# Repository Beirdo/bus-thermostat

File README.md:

# bus-thermostat
Interface to connect a standard thermostat to a Webasto Thermo Top C for my bus

60Hz oscillator design inspired by https://www.youtube.com/watch?v=BfqGnwAhldA

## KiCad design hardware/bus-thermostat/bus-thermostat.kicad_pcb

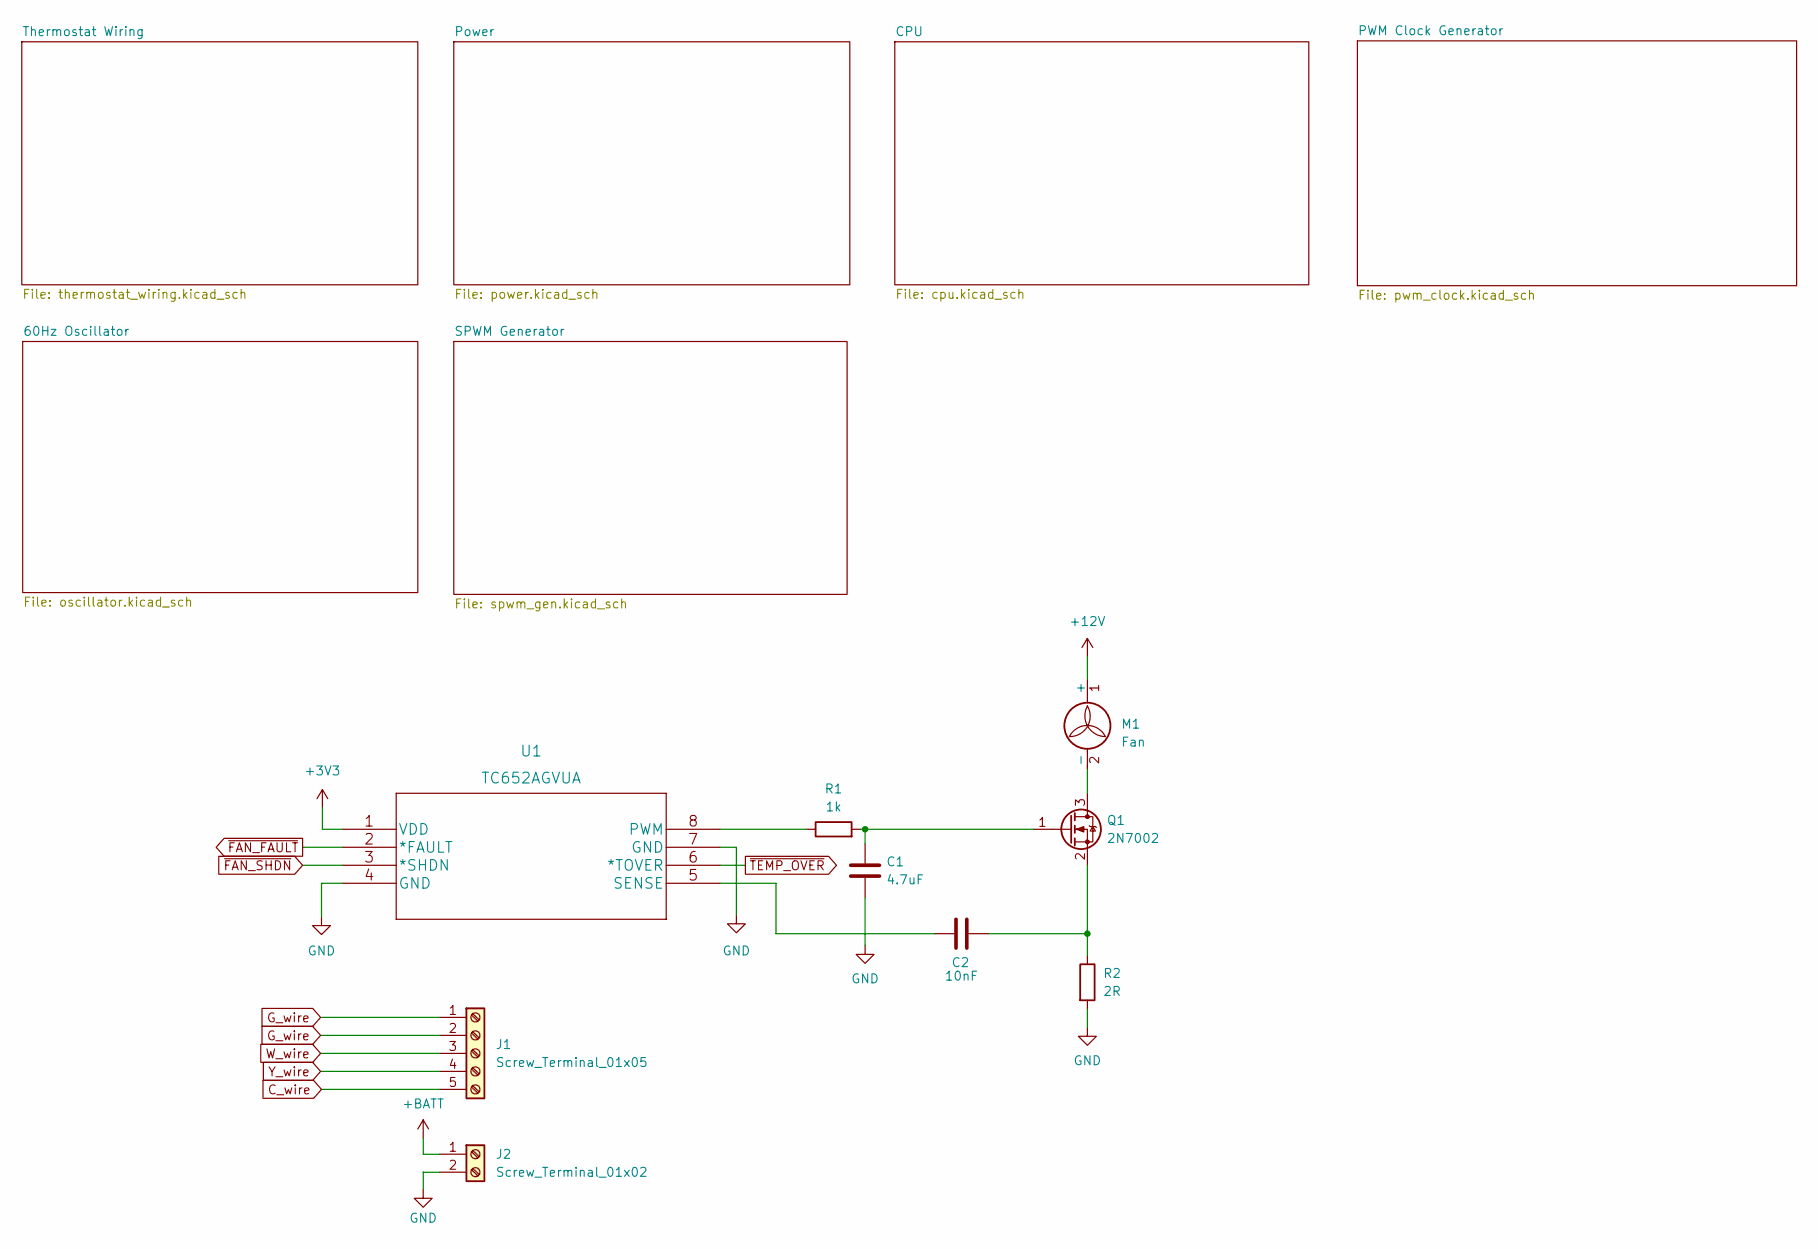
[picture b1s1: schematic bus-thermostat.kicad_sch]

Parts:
C1: 4.7uF; C_0805_2012Metric_Pad1.18x1.45mm_HandSolder
C2: 10nF; C_0805_2012Metric_Pad1.18x1.45mm_HandSolder
J1: Screw_Terminal_01x05; TerminalBlock_TE_282834-5_1x05_P2.54mm_Horizontal
J2: Screw_Terminal_01x02; TerminalBlock_TE_282834-2_1x02_P2.54mm_Horizontal
M1: Fan; PinHeader_1x02_P1.00mm_Vertical
Q1: 2N7002; SOT-23
R1: 1k; R_0805_2012Metric_Pad1.20x1.40mm_HandSolder
R2: 2R; R_0805_2012Metric_Pad1.20x1.40mm_HandSolder
U1: TC652AGVUA

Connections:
+3V3: U1.1 (VDD); also elsewhere on the board
+12V: M1.1 (+); also elsewhere on the board
+BATT: J2.1; also elsewhere on the board
C_wire: J1.5; also elsewhere on the board
GND: C1.2, J2.2, R2.2, U1.4 (GND), U1.7 (GND); also elsewhere on the board
G_wire: J1.2; also elsewhere on the board
unnamed: C1.1, Q1.1 (G), R1.2
unnamed: C2.1, U1.5 (SENSE)
unnamed: C2.2, Q1.2 (S), R2.1
unnamed: M1.2 (-), Q1.3 (D)
unnamed: R1.1, U1.8 (PWM)
W_wire: J1.3; also elsewhere on the board
Y_wire: J1.4; also elsewhere on the board
~FAN_FAULT: U1.2 (*FAULT); also elsewhere on the board
~FAN_SHDN: U1.3 (*SHDN); also elsewhere on the board
~TEMP_OVER: U1.6 (*TOVER); also elsewhere on the board

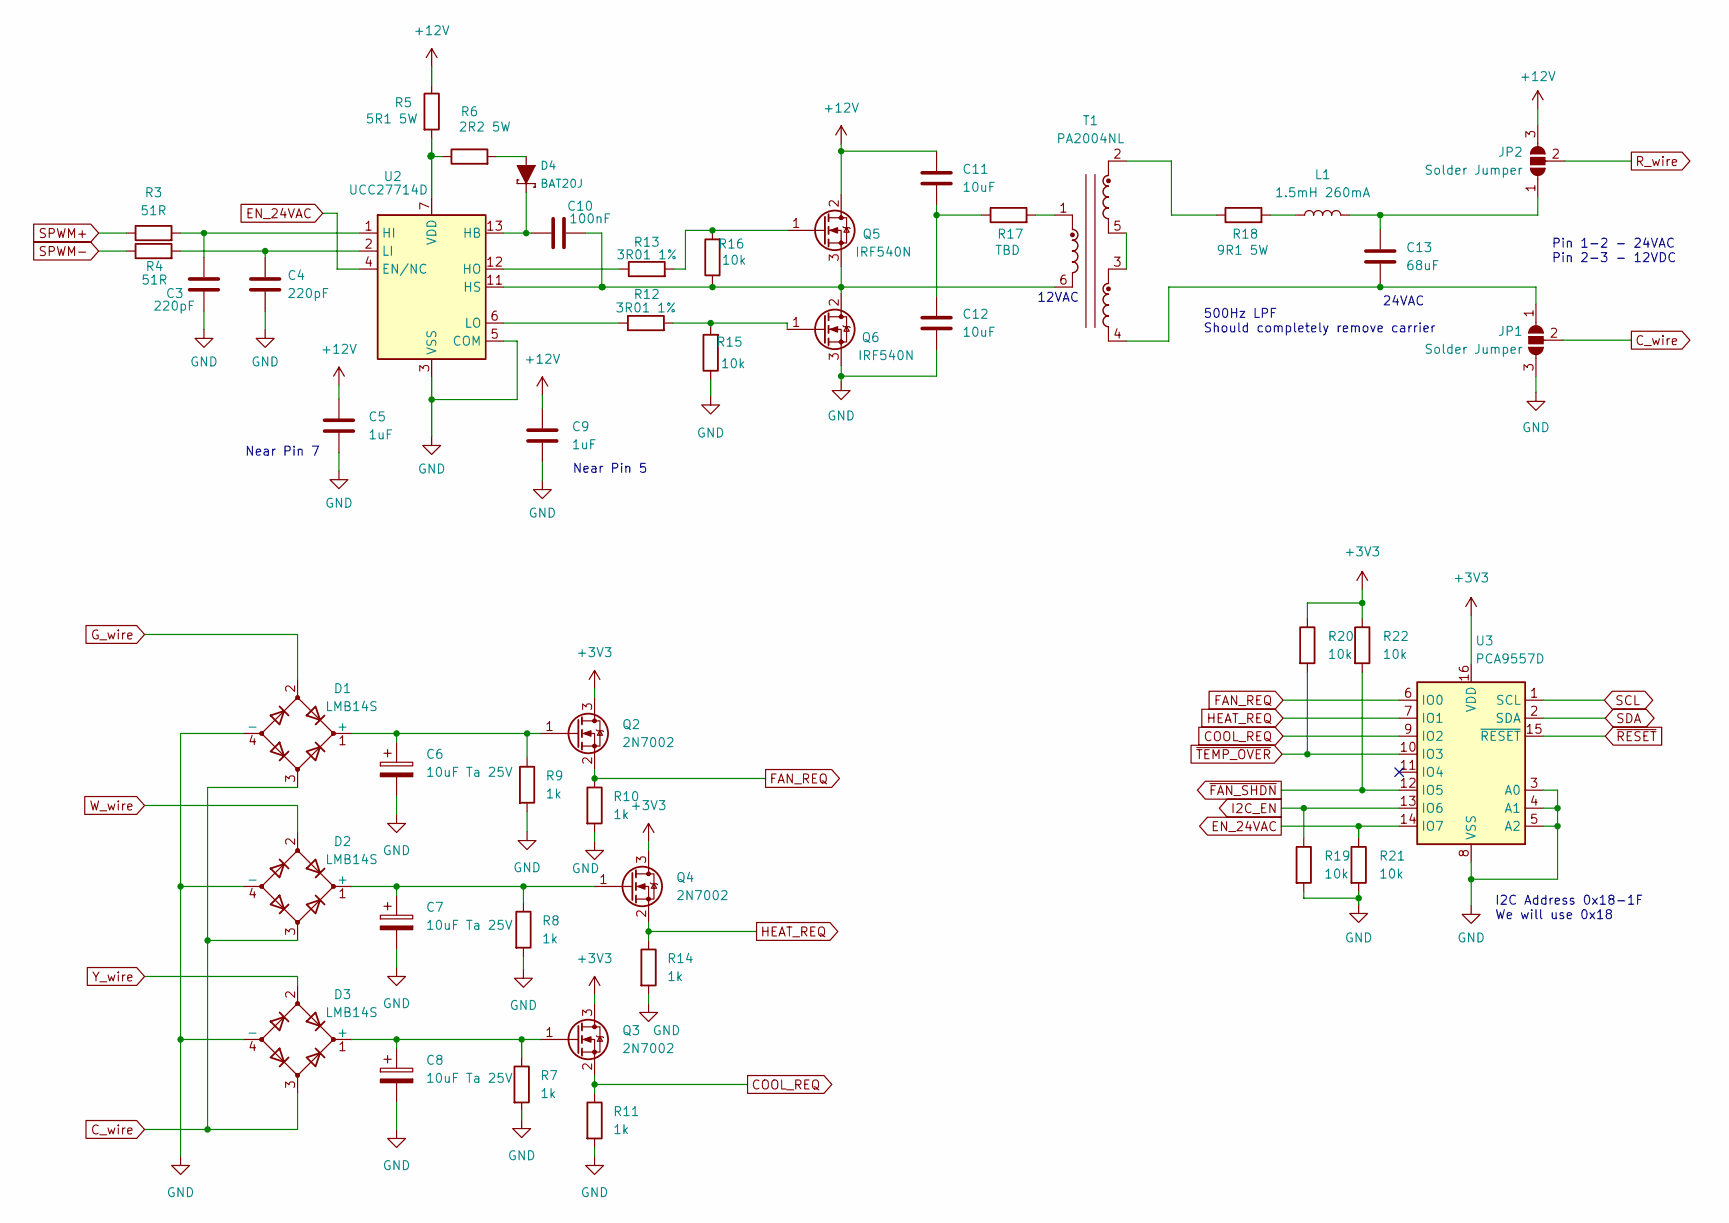
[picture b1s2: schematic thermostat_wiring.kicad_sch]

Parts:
C3, C4: 220pF; C_0805_2012Metric_Pad1.18x1.45mm_HandSolder
C5, C9: 1uF; C_0805_2012Metric_Pad1.18x1.45mm_HandSolder
C6, C7, C8: 10uF Ta 25V; CP_EIA-6032-20_AVX-F_Pad2.25x2.35mm_HandSolder
C10: 100nF; C_0805_2012Metric_Pad1.18x1.45mm_HandSolder
C11, C12: 10uF; C_0805_2012Metric_Pad1.18x1.45mm_HandSolder
C13: 68uF; C_0805_2012Metric_Pad1.18x1.45mm_HandSolder
D1, D2, D3: LMB14S; Diode_Bridge_Vishay_MBLS
D4: BAT20J; SOD-323
JP1, JP2: Solder Jumper; SolderJumper-3_P2.0mm_Open_TrianglePad1.0x1.5mm
L1: 1.5mH 260mA; L_Radial_D28.0mm_P29.20mm
Q2, Q3, Q4: 2N7002; SOT-23
Q5, Q6: IRF540N; TO-220-3_Vertical
R3, R4: 51R; R_0805_2012Metric_Pad1.20x1.40mm_HandSolder
R5: 5R1 5W; 355010RFT
R6: 2R2 5W; 355010RFT
R7, R8, R9, R10, R11, R14: 1k; R_0805_2012Metric_Pad1.20x1.40mm_HandSolder
R12, R13: 3R01 1%; R_0805_2012Metric_Pad1.20x1.40mm_HandSolder
R15, R16, R19, R20, R21, R22: 10k; R_0805_2012Metric_Pad1.20x1.40mm_HandSolder
R17: TBD; R_0805_2012Metric_Pad1.20x1.40mm_HandSolder
R18: 9R1 5W; 355010RFT
T1: PA2004NL; Pulse_PA2004NL
U2: UCC27714D; SOIC-14_3.9x8.7mm_P1.27mm
U3: PCA9557D; SOP-16_3.9x9.9mm_P1.27mm

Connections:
+3V3: Q2.3 (D), Q3.3 (D), Q4.3 (D), R20.1, R22.1, U3.16 (VDD); also elsewhere on the board
+12V: C5.1, C9.1, C11.1, JP2.3 (B), Q5.2 (D), R5.1; also elsewhere on the board
COOL_REQ: Q3.2 (S), R11.1, U3.9 (IO2)
C_wire: D1.3, D2.3, D3.3, JP1.2 (C); also elsewhere on the board
EN_24VAC: R21.1, U2.4 (EN/NC), U3.14 (IO7)
FAN_REQ: Q2.2 (S), R10.1, U3.6 (IO0)
GND: C3.2, C4.2, C5.2, C6.2, C7.2, C8.2, C9.2, C12.2, D1.4 (-), D2.4 (-), D3.4 (-), JP1.3 (B), Q6.3 (S), R7.2, R8.2, R9.2, R10.2, R11.2, R14.2, R15.1, R19.2, R21.2, U2.3 (VSS), U2.5 (COM), U3.3 (A0), U3.4 (A1), U3.5 (A2), U3.8 (VSS); also elsewhere on the board
G_wire: D1.2; also elsewhere on the board
HEAT_REQ: Q4.2 (S), R14.1, U3.7 (IO1)
I2C_EN: R19.1, U3.13 (IO6); also elsewhere on the board
unnamed: C3.1, R3.2, U2.1 (HI)
unnamed: C4.1, R4.2, U2.2 (LI)
unnamed: C6.1, D1.1 (+), Q2.1 (G), R9.1
unnamed: C7.1, D2.1 (+), Q4.1 (G), R8.1
unnamed: C8.1, D3.1 (+), Q3.1 (G), R7.1
unnamed: C10.1, D4.C, U2.13 (HB)
unnamed: C10.2, U2.11 (HS)
unnamed: C11.2, C12.1, R17.1
unnamed: C13.1, JP2.1 (A), L1.2
unnamed: C13.2, JP1.1 (A), T1.4
unnamed: D4.A, R6.2
unnamed: L1.1, R18.2
unnamed: Q5.1 (G), R13.2, R16.2
unnamed: Q5.3 (S), Q6.2 (D), R16.1, T1.6
unnamed: Q6.1 (G), R12.2, R15.2
unnamed: R5.2, R6.1, U2.7 (VDD)
unnamed: R12.1, U2.6 (LO)
unnamed: R13.1, U2.12 (HO)
unnamed: R17.2, T1.1
unnamed: R18.1, T1.2
unnamed: T1.3, T1.5
R_wire: JP2.2 (C)
SCL: U3.1 (SCL); also elsewhere on the board
SDA: U3.2 (SDA); also elsewhere on the board
SPWM+: R3.1; also elsewhere on the board
SPWM-: R4.1; also elsewhere on the board
W_wire: D2.2; also elsewhere on the board
Y_wire: D3.2; also elsewhere on the board
~FAN_SHDN: R22.2, U3.12 (IO5); also elsewhere on the board
~RESET: U3.15 (~RESET); also elsewhere on the board
~TEMP_OVER: R20.2, U3.10 (IO3); also elsewhere on the board

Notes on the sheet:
Near Pin 5
Pin 1-2 - 24VAC Pin 2-3 - 12VDC
500Hz LPF Should completely remove carrier
12VAC
Near Pin 7
24VAC
I2C Address 0x18-1F We will use 0x18

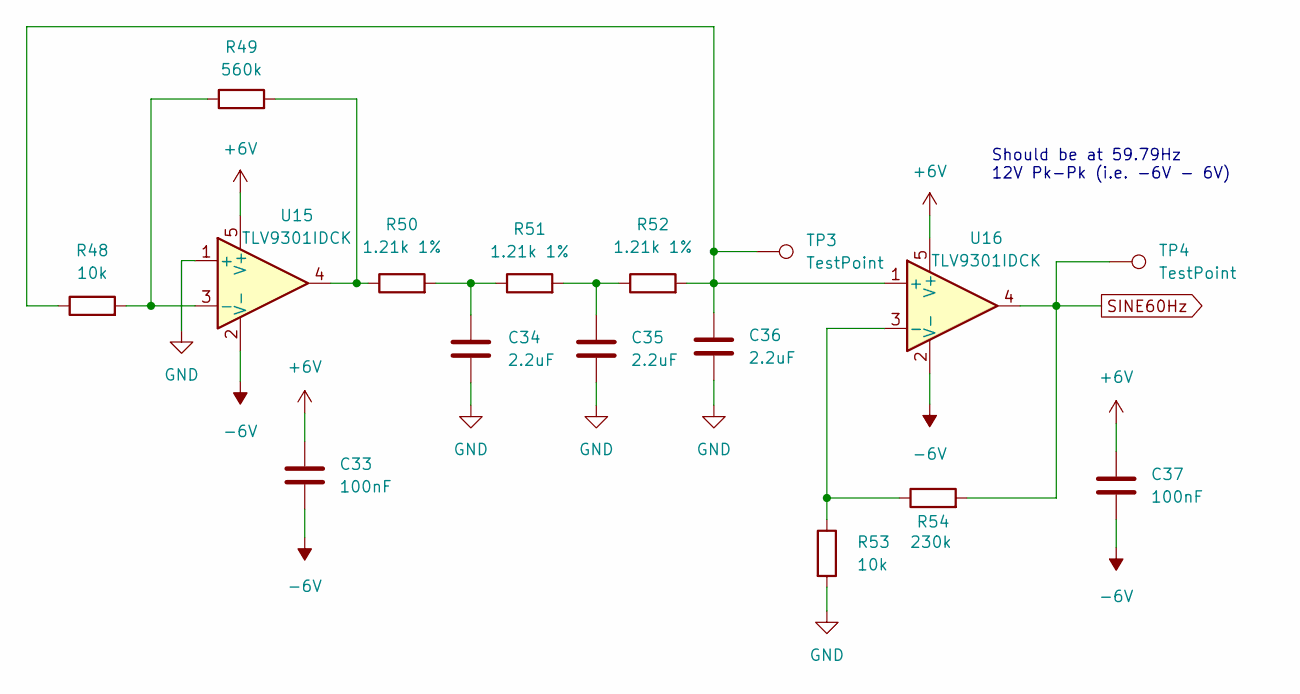
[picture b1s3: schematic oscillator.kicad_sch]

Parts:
C33, C37: 100nF; C_0805_2012Metric_Pad1.18x1.45mm_HandSolder
C34, C35, C36: 2.2uF; C_0805_2012Metric_Pad1.18x1.45mm_HandSolder
R48, R53: 10k; R_0805_2012Metric_Pad1.20x1.40mm_HandSolder
R49: 560k; R_0805_2012Metric_Pad1.20x1.40mm_HandSolder
R50, R51, R52: 1.21k 1%; R_0805_2012Metric_Pad1.20x1.40mm_HandSolder
R54: 230k; R_0805_2012Metric_Pad1.20x1.40mm_HandSolder
TP3, TP4: TestPoint; Pin_D0.7mm_L6.5mm_W1.8mm_FlatFork
U15, U16: TLV9301IDCK; SOT-353_SC-70-5

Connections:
+6V: C33.1, C37.1, U15.5 (V+), U16.5 (V+); also elsewhere on the board
-6V: C33.2, C37.2, U15.2 (V-), U16.2 (V-); also elsewhere on the board
GND: C34.1, C35.1, C36.1, R53.2, U15.1 (+); also elsewhere on the board
unnamed: C34.2, R50.2, R51.1
unnamed: C35.2, R51.2, R52.1
unnamed: C36.2, R48.1, R52.2, TP3.1, U16.1 (+)
unnamed: R48.2, R49.1, U15.3 (-)
unnamed: R49.2, R50.1, U15.4
unnamed: R53.1, R54.1, U16.3 (-)
SINE60Hz: R54.2, TP4.1, U16.4; also elsewhere on the board

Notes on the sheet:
Should be at 59.79Hz 12V Pk-Pk (i.e. -6V - 6V)

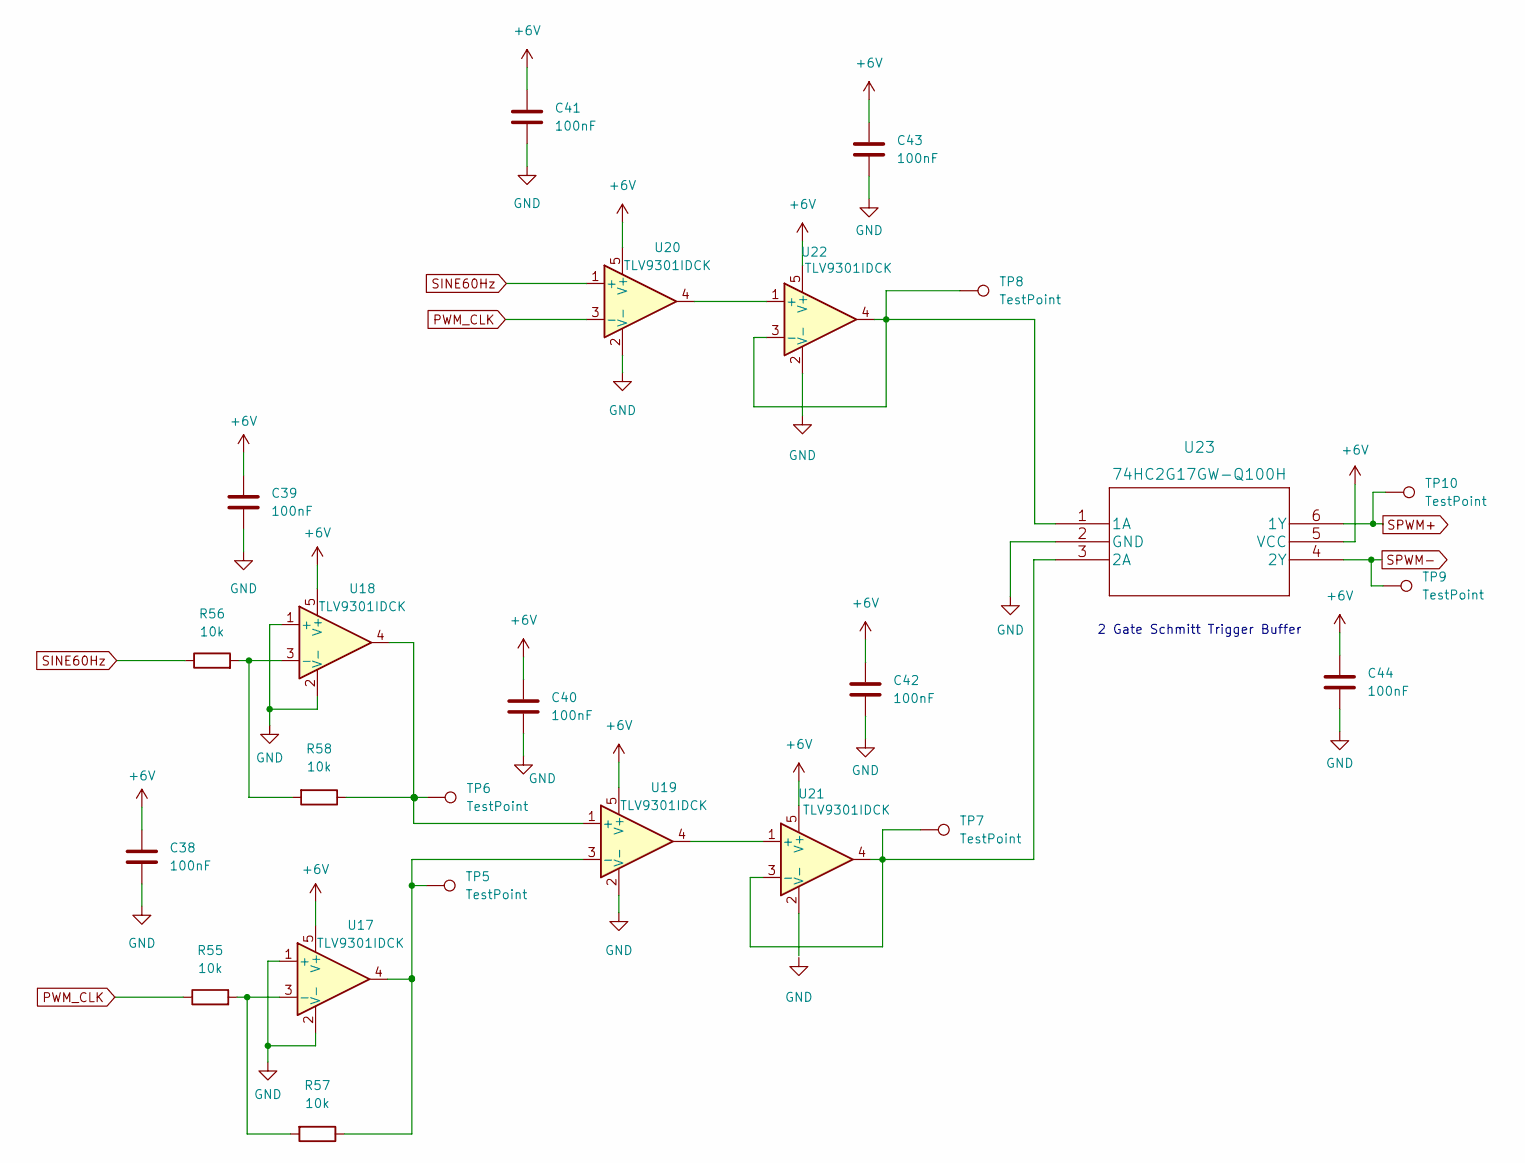
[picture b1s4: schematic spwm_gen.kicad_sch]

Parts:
C38, C39, C40, C41, C42, C43, C44: 100nF; C_0805_2012Metric_Pad1.18x1.45mm_HandSolder
R55, R56, R57, R58: 10k; R_0805_2012Metric_Pad1.20x1.40mm_HandSolder
TP5, TP6, TP7, TP8, TP9, TP10: TestPoint; Pin_D0.7mm_L6.5mm_W1.8mm_FlatFork
U17, U18, U19, U20, U21, U22: TLV9301IDCK; SOT-353_SC-70-5
U23: 74HC2G17GW-Q100H

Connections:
+6V: C38.1, C39.1, C40.1, C41.1, C42.1, C43.1, C44.1, U17.5 (V+), U18.5 (V+), U19.5 (V+), U20.5 (V+), U21.5 (V+), U22.5 (V+), U23.5 (VCC); also elsewhere on the board
GND: C38.2, C39.2, C40.2, C41.2, C42.2, C43.2, C44.2, U17.1 (+), U17.2 (V-), U18.1 (+), U18.2 (V-), U19.2 (V-), U20.2 (V-), U22.2 (V-), U23.2 (GND); also elsewhere on the board
unnamed: R55.2, R57.2, U17.3 (-)
unnamed: R56.2, R58.2, U18.3 (-)
unnamed: R57.1, U17.4
unnamed: R58.1, U18.4, U19.1 (+)
unnamed: TP5.1, U19.3 (-)
unnamed: TP7.1, U21.3 (-), U21.4, U23.3 (2A)
unnamed: TP8.1, U22.3 (-), U22.4, U23.1 (1A)
unnamed: U19.4, U21.1 (+)
unnamed: U20.4, U22.1 (+)
PWM_CLK: R55.1, U20.3 (-); also elsewhere on the board
SINE60Hz: R56.1, U20.1 (+); also elsewhere on the board
SPWM+: TP10.1, U23.6 (1Y); also elsewhere on the board
SPWM-: TP9.1, U23.4 (2Y); also elsewhere on the board

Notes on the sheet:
2 Gate Schmitt Trigger Buffer

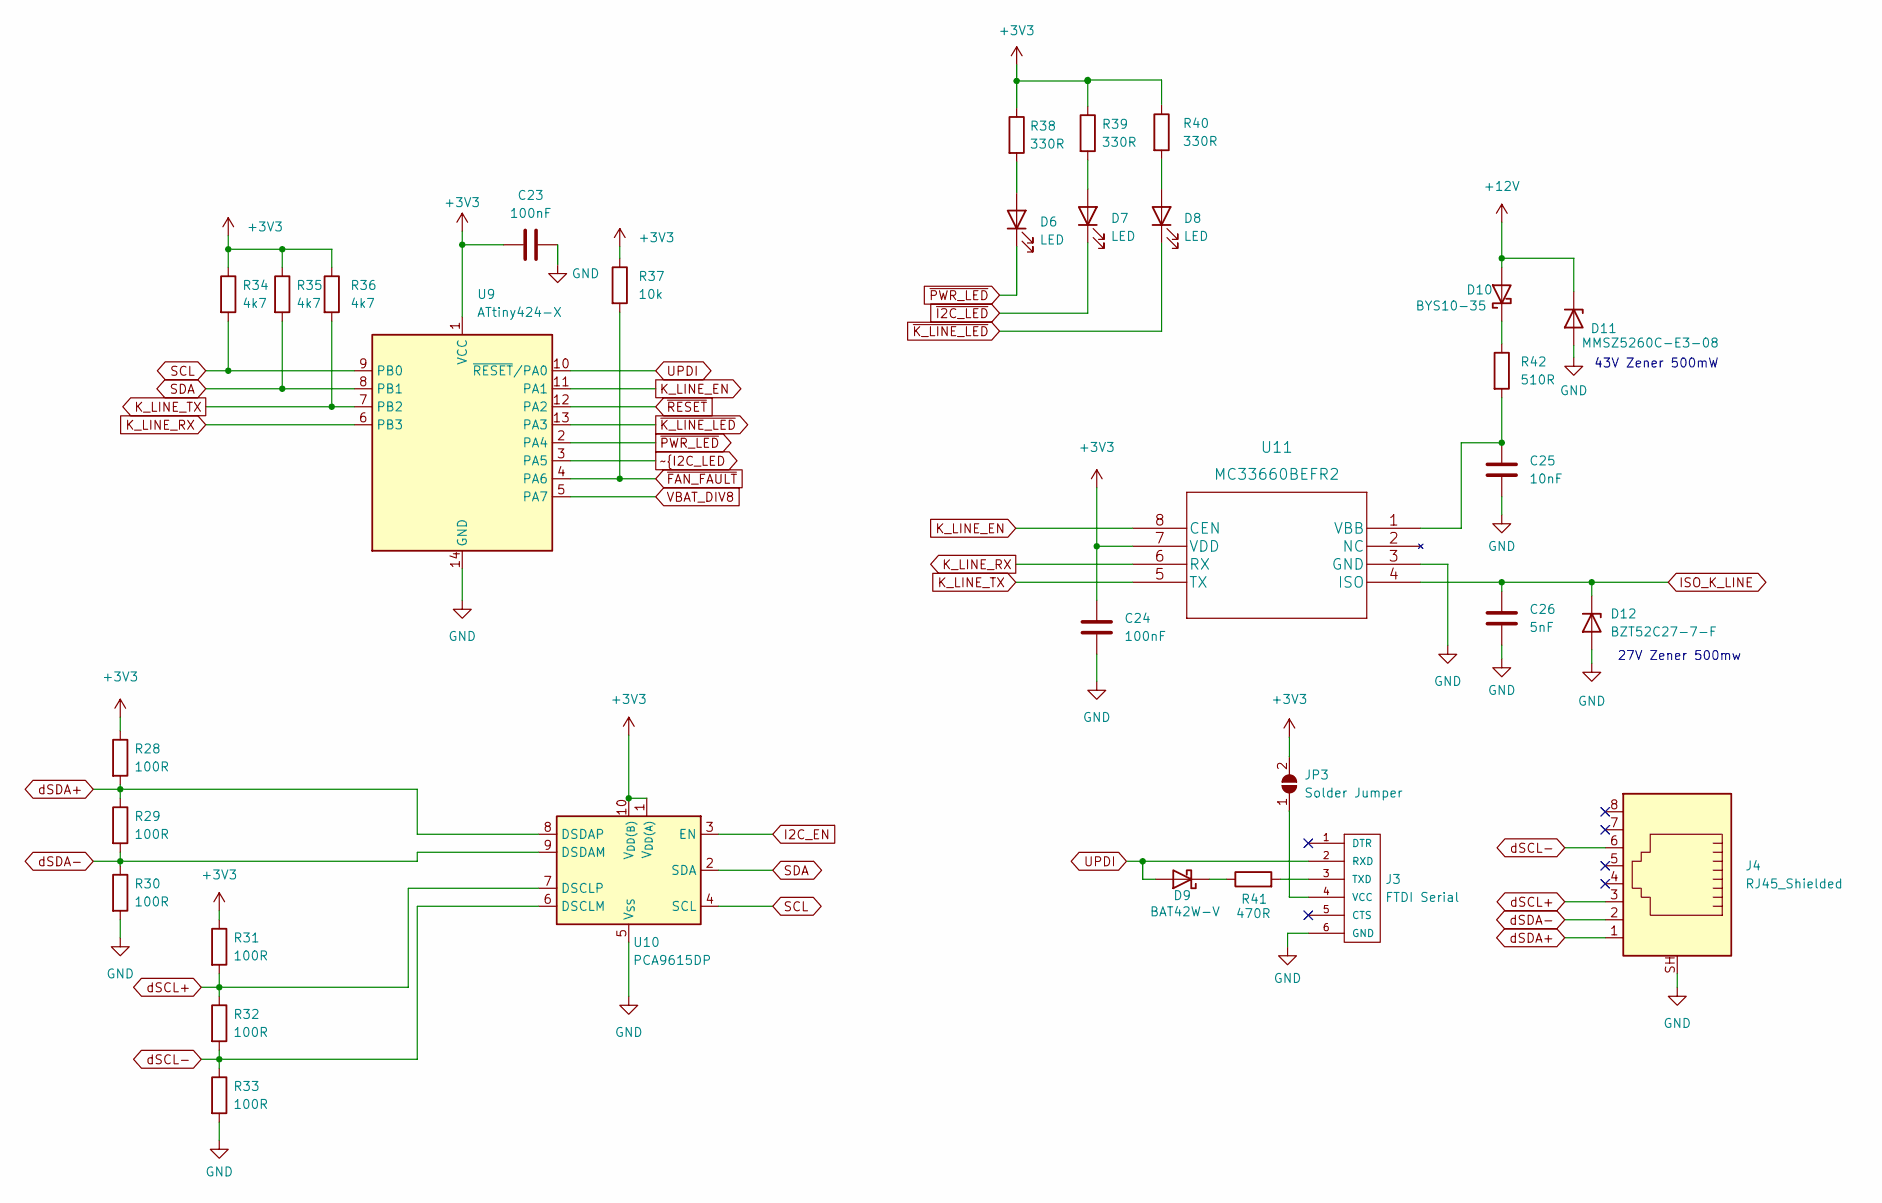
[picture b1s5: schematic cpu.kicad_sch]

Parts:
C23, C24: 100nF; C_0805_2012Metric_Pad1.18x1.45mm_HandSolder
C25: 10nF; C_0805_2012Metric_Pad1.18x1.45mm_HandSolder
C26: 5nF; C_0805_2012Metric_Pad1.18x1.45mm_HandSolder
D6, D7, D8: LED; LED_0805_2012Metric_Pad1.15x1.40mm_HandSolder
D9: BAT42W-V; D_SOD-123
D10: BYS10-35; D_SMA_Handsoldering
D11: MMSZ5260C-E3-08; D_SOD-123
D12: BZT52C27-7-F; D_SOD-123
J3: FTDI Serial; FTDI-TARGET
J4: RJ45_Shielded; RJ45-8
JP3: Solder Jumper; SolderJumper-2_P1.3mm_Open_TrianglePad1.0x1.5mm
R28, R29, R30, R31, R32, R33: 100R; R_0805_2012Metric_Pad1.20x1.40mm_HandSolder
R34, R35, R36: 4k7; R_0805_2012Metric_Pad1.20x1.40mm_HandSolder
R37: 10k; R_0805_2012Metric_Pad1.20x1.40mm_HandSolder
R38, R39, R40: 330R; R_0805_2012Metric_Pad1.20x1.40mm_HandSolder
R41: 470R; R_0805_2012Metric_Pad1.20x1.40mm_HandSolder
R42: 510R; R_0805_2012Metric_Pad1.20x1.40mm_HandSolder
U9: ATtiny424-X; TSSOP-14_4.4x5mm_P0.65mm
U10: PCA9615DP; TSSOP-10_3x3mm_P0.5mm
U11: MC33660BEFR2

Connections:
+3V3: C23.2, C24.1, JP3.2 (B), R28.1, R31.1, R34.1, R35.1, R36.1, R37.1, R38.1, R39.1, U9.1 (VCC), U10.1 (V_{DD(A)}), U10.10 (V_{DD(B)}), U11.7 (VDD); also elsewhere on the board
+12V: D10.2 (A), D11.1 (K); also elsewhere on the board
GND: C23.1, C24.2, C25.2, C26.2, D11.2 (A), D12.2 (A), J3.6 (GND), J4.SH, R30.2, R33.2, U9.14 (GND), U10.5 (V_{SS}), U11.3 (GND); also elsewhere on the board
I2C_EN: U10.3 (EN); also elsewhere on the board
ISO_K_LINE: C26.1, D12.1 (K), U11.4 (ISO)
K_LINE_EN: U9.11 (PA1), U11.8 (CEN)
K_LINE_RX: U9.6 (PB3), U11.6 (RX)
K_LINE_TX: R36.2, U9.7 (PB2), U11.5 (TX)
unnamed: C25.1, R42.2, U11.1 (VBB)
unnamed: D6.2 (A), R38.2
unnamed: D7.2 (A), R39.2
unnamed: D8.2 (A), R40.2
unnamed: D9.1 (K), R41.1
unnamed: D10.1 (K), R42.1
unnamed: J3.4 (VCC), JP3.1 (A)
unnamed: J3.3 (TXD), R41.2
SCL: R34.2, U9.9 (PB0), U10.4 (SCL); also elsewhere on the board
SDA: R35.2, U9.8 (PB1), U10.2 (SDA); also elsewhere on the board
UPDI: D9.2 (A), J3.2 (RXD), U9.10 (~RESET/PA0)
VBAT_DIV8: U9.5 (PA7); also elsewhere on the board
dSCL+: J4.3, R31.2, R32.1, U10.7 (DSCLP)
dSCL-: J4.6, R32.2, R33.1, U10.6 (DSCLM)
dSDA+: J4.1, R28.2, R29.1, U10.8 (DSDAP)
dSDA-: J4.2, R29.2, R30.1, U10.9 (DSDAM)
~FAN_FAULT: R37.2, U9.4 (PA6); also elsewhere on the board
~K_LINE_LED: D8.1 (K), U9.13 (PA3)
~PWR_LED: D6.1 (K), U9.2 (PA4)
~RESET: U9.12 (PA2); also elsewhere on the board

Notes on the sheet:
27V Zener 500mw
43V Zener 500mW

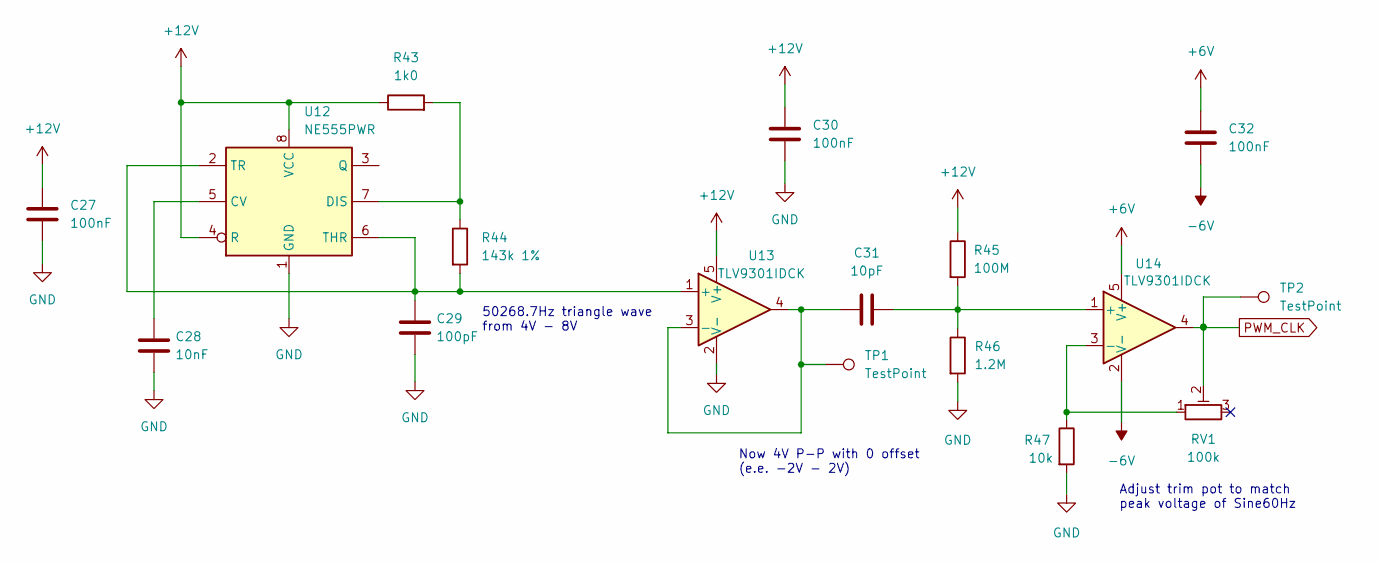
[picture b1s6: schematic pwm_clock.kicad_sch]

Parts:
C27, C30, C32: 100nF; C_0805_2012Metric_Pad1.18x1.45mm_HandSolder
C28: 10nF; C_0805_2012Metric_Pad1.18x1.45mm_HandSolder
C29: 100pF; C_0805_2012Metric_Pad1.18x1.45mm_HandSolder
C31: 10pF; C_0805_2012Metric_Pad1.18x1.45mm_HandSolder
R43: 1k0; R_0805_2012Metric_Pad1.20x1.40mm_HandSolder
R44: 143k 1%; R_0805_2012Metric_Pad1.20x1.40mm_HandSolder
R45: 100M; R_0805_2012Metric_Pad1.20x1.40mm_HandSolder
R46: 1.2M; R_0805_2012Metric_Pad1.20x1.40mm_HandSolder
R47: 10k; R_0805_2012Metric_Pad1.20x1.40mm_HandSolder
RV1: 100k; R_0805_2012Metric_Pad1.20x1.40mm_HandSolder
TP1, TP2: TestPoint; Pin_D0.7mm_L6.5mm_W1.8mm_FlatFork
U12: NE555PWR; TSSOP-8_4.4x3mm_P0.65mm
U13, U14: TLV9301IDCK; SOT-353_SC-70-5

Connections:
+6V: C32.1, U14.5 (V+); also elsewhere on the board
+12V: C27.1, C30.1, R43.1, R45.1, U12.4 (R), U12.8 (VCC), U13.5 (V+); also elsewhere on the board
-6V: C32.2, U14.2 (V-); also elsewhere on the board
GND: C27.2, C28.2, C29.2, C30.2, R46.2, R47.2, U12.1 (GND), U13.2 (V-); also elsewhere on the board
unnamed: C28.1, U12.5 (CV)
unnamed: C29.1, R44.2, U12.2 (TR), U12.6 (THR), U13.1 (+)
unnamed: C31.1, TP1.1, U13.3 (-), U13.4
unnamed: C31.2, R45.2, R46.1, U14.1 (+)
unnamed: R43.2, R44.1, U12.7 (DIS)
unnamed: R47.1, RV1.1, U14.3 (-)
PWM_CLK: RV1.2, TP2.1, U14.4; also elsewhere on the board

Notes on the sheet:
50268.7Hz triangle wave from 4V - 8V
Adjust trim pot to match peak voltage of Sine60Hz
Now 4V P-P with 0 offset (e.e. -2V - 2V)

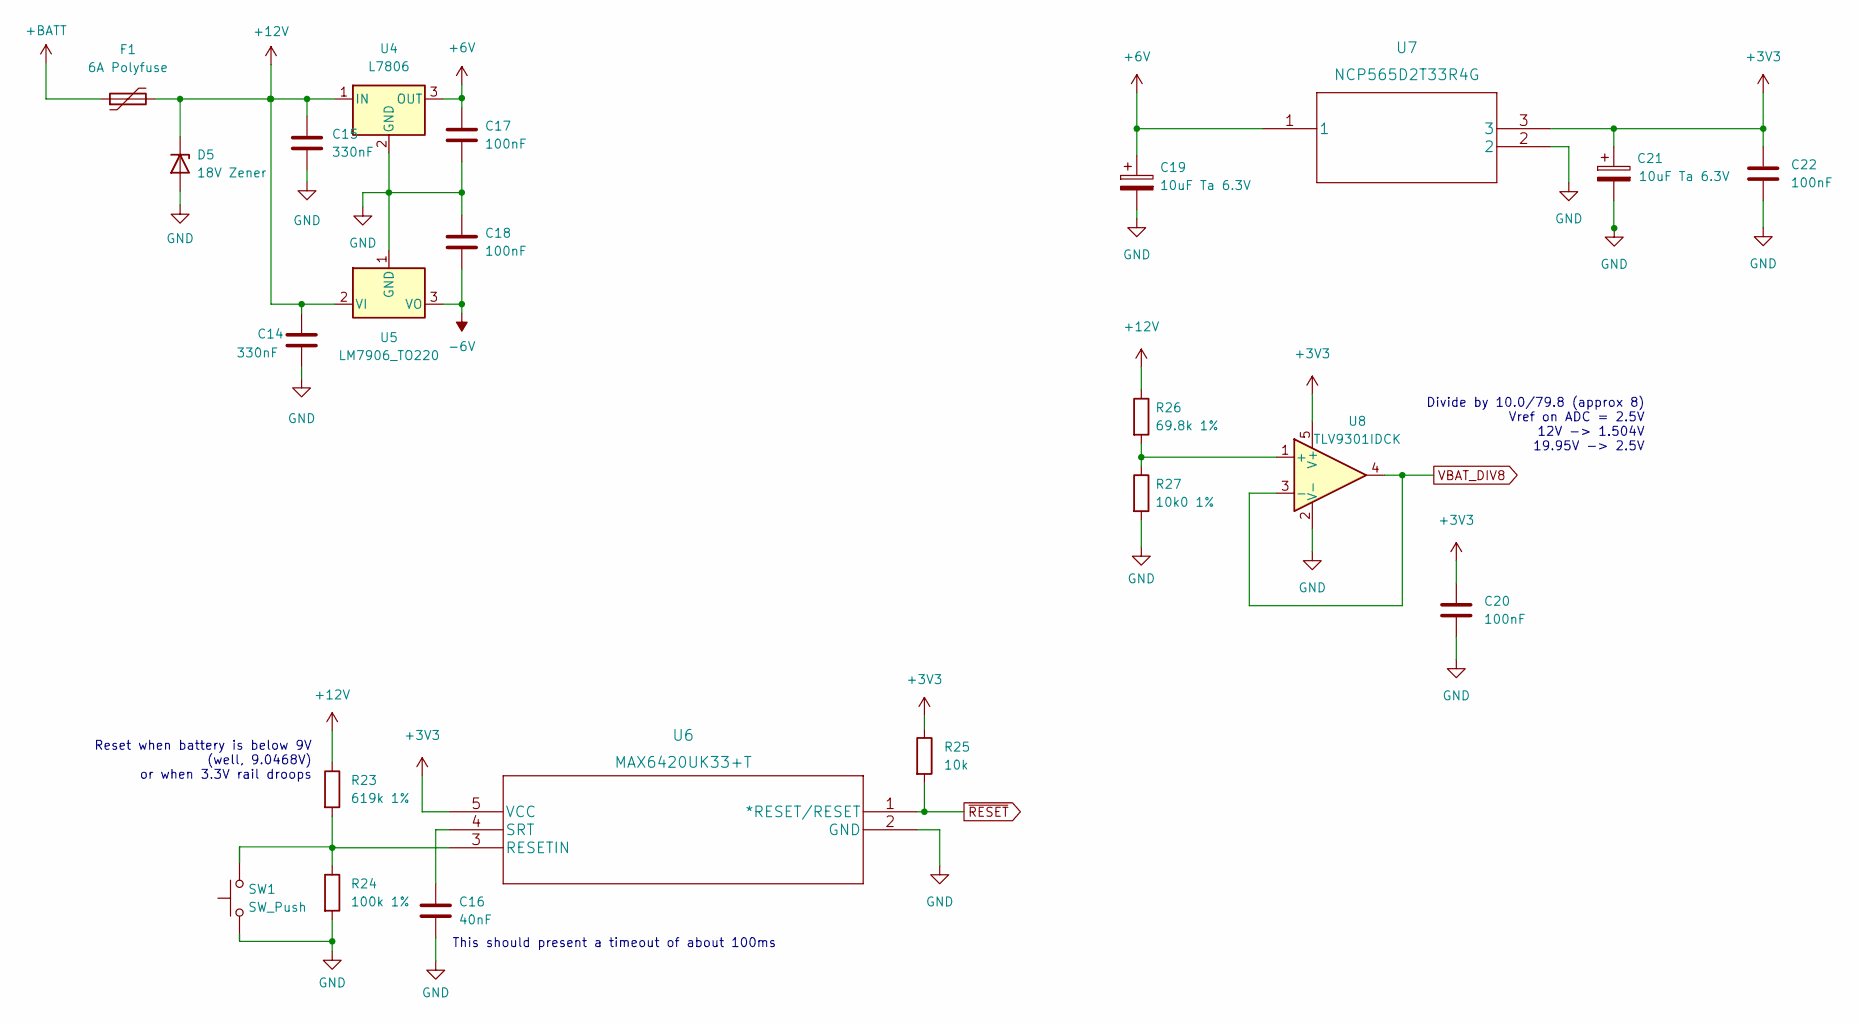
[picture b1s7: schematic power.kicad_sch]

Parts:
C14, C15: 330nF; C_0805_2012Metric_Pad1.18x1.45mm_HandSolder
C16: 40nF; C_0805_2012Metric_Pad1.18x1.45mm_HandSolder
C17, C18, C20, C22: 100nF; C_0805_2012Metric_Pad1.18x1.45mm_HandSolder
C19, C21: 10uF Ta 6.3V; CP_EIA-3216-18_Kemet-A_Pad1.58x1.35mm_HandSolder
D5: 18V Zener; D_SOD-123
F1: 6A Polyfuse; R_0603_1608Metric_Pad0.98x0.95mm_HandSolder; Digikey 18-0603L175SLYRTCT-ND
R23: 619k 1%; R_0805_2012Metric_Pad1.20x1.40mm_HandSolder
R24: 100k 1%; R_0805_2012Metric_Pad1.20x1.40mm_HandSolder
R25: 10k; R_0805_2012Metric_Pad1.20x1.40mm_HandSolder
R26: 69.8k 1%; R_0805_2012Metric_Pad1.20x1.40mm_HandSolder
R27: 10k0 1%; R_0805_2012Metric_Pad1.20x1.40mm_HandSolder
SW1: SW_Push; TACTILE_SWITCH_PTH_6.0MM
U4: L7806; TO-220-3_Vertical
U5: LM7906_TO220; TO-220-3_Vertical
U6: MAX6420UK33+T; MAX6420UK33&plus_T
U7: NCP565D2T33R4G
U8: TLV9301IDCK; SOT-353_SC-70-5

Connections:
+3V3: C20.1, C21.1, C22.1, R25.1, U6.5 (VCC), U7.3, U8.5 (V+); also elsewhere on the board
+6V: C19.1, U7.1; also elsewhere on the board
+12V: C14.1, C15.1, R23.1, R26.1, U4.1 (IN), U5.2 (VI); also elsewhere on the board
+BATT: F1.1; also elsewhere on the board
-6V: C18.2, U5.3 (VO); also elsewhere on the board
GND: C14.2, C15.2, C16.2, C17.2, C18.1, C19.2, C20.2, C22.2, D5.2 (A), R24.2, R27.2, SW1.1, U4.2 (GND), U5.1 (GND), U6.2 (GND), U7.2, U8.2 (V-); also elsewhere on the board
unnamed: C16.1, U6.4 (SRT)
unnamed: C17.1, U4.3 (OUT)
unnamed: D5.1 (K), F1.2
unnamed: R23.2, R24.1, U6.3 (RESETIN)
unnamed: R26.2, R27.1, U8.1 (+)
VBAT_DIV8: U8.3 (-), U8.4; also elsewhere on the board
~RESET: R25.2, U6.1 (*RESET/RESET); also elsewhere on the board

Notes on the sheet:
Divide by 10.0/79.8 (approx 8) Vref on ADC = 2.5V 12V -> 1.504V 19.95V -> 2.5V
Reset when battery is below 9V (well, 9.0468V) or when 3.3V rail droops
This should present a timeout of about 100ms

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
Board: 2 copper layers, 167 parts (0 on the bottom side), 98 nets, no tracks yet.

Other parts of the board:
locked: Heatsink_Fischer_SK104-STC-STIC_35x13mm_2xDrill2.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; Heatsink_Fischer_SK104-STC-STIC_35x13mm_2xDrill2.5mm

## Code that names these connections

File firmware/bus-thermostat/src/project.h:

#ifndef __project_h_
#define __project_h_

#include <Arduino.h>
#include <Beirdo-Utilities.h>

#define PIN_UPDI	PIN_PA0
#define PIN_KLINE_EN    PIN_PA1
#define PIN_RESET       PIN_PA2
#define PIN_KLINE_LED   PIN_PA3
#define PIN_PWR_LED     PIN_PA4
#define PIN_I2C_LED     PIN_PA5
#define PIN_FAN_FAULT   PIN_PA6
#define PIN_VBAT_DIV8   PIN_PA7
#define PIN_SCL         PIN_PB0
#define PIN_SDA         PIN_PB1
#define PIN_KLINE_TX    PIN_PB2
#define PIN_KLINE_RX    PIN_PB3

// PCA9557 Pins
#define PIN_FAN_REQ     0
#define PIN_HEAT_REQ    1
#define PIN_COOL_REQ    2
#define PIN_TEMP_OVER	3
#define PIN_FAN_SHDN	5
#define PIN_EX_I2C_EN   6
#define PIN_EN_24VAC    7

#define I2C_ADDR_PCA9557  0x18

#endif

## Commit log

2023-01-27 Initial checkin
2023-01-27 Trying to fix submodules
2023-02-02 Changing the SPWM around
2023-02-03 Redid the 24VAC path entirely.
2023-02-03 First rev of thermostat firmware
2023-02-03 Add the README.md
2023-02-03 Oops, missed a line
2023-02-06 OK, we will need the R wire! Also put in option to use 12VDC
2023-02-06 Add some text
2023-02-06 Rework the AC path generation again. Opamps only.
    - awaiting the completion of analog circuit analysis
2023-02-07 Update some components
2023-02-07 Adjust PWMClock to 50kHz, use pulse transformers
2023-02-07 More slight tweaks for resimulation
2023-02-07 Add datasheets
    - got all but a few diodes (some zeners and a schottky)
2023-02-07 Fix oscillator, add fan controller/thermostat and its IOs.
2023-02-07 Ooops forgot to save.
2023-02-09 Added serial ports
2023-02-09 Add in the TINA schematic and pspice exported netlist
2023-02-25 Misc changes, move the git libs to new repo
    - https://github.com/Beirdo/KiCad-Git-Libraries
2023-03-05 Moved over to PlatformIO
2023-03-06 Move away from .ino
2023-03-07 Moved bus-thermostat to lib_deps

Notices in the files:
parts and their libraries:
Copyright 2021 Accelerated Designs. All rights reserved.
